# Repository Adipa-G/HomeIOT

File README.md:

# HomeIOT 🏠

A comprehensive IoT platform for managing embedded devices (ESP32/Pico). This platform supports creating modules in the serverside, assigning to devices so that these can be executed on the edge devices so that result is visible on the server.

## Key Features

- **Device Management**: Add devices from the web UI with one downloaded `main.py`, then monitor and control them across platforms (ESP32, Raspberry Pi Pico)
- **Module System**: Deploy and manage versioned Python modules on devices with remote execution and result tracking
- **Interactive Dev Commands**: Execute arbitrary Python code on devices for debugging and testing
- **Dashboard Analytics**: Real-time metrics on device health, module activity, and system status. The dashboard supports visual elements such as graphs and guages.
- **OTA Updates**: Over-the-air firmware updates with rollback support
- **Comprehensive Logging**: Device logs, module results, and execution tracking for troubleshooting

## Quick Start

### 

### Running the Server (30 seconds)

**Option 1: Direct .NET Execution** (for development)
```bash
# Clone and navigate to project
git clone <repo-url>
cd HomeIOT

# Run the API server
dotnet run --project api/src/api.csproj
```

Server starts at: `http://localhost:5228`

**Option 2: Docker Compose** (for easy setup)
```bash
docker-compose up -d
```

Server accessible at: `http://localhost:5228` (or your configured hostname)

### Initial Login

1. Open `http://localhost:5228` in your browser
2. Login with credentials:
   - **Username**: `Admin`
   - **Password**: `123`
3. ⚠️ **IMPORTANT**: Change the admin password immediately in the Web UI (Users section)
4. Verify setup: Dashboard should display "0 devices online"

---

## Project Structure

```
HomeIOT/
├── api/                    # .NET 10 Backend API
│   ├── src/               # API source code (controllers, services, data)
│   └── tests/             # xUnit tests
├── edge/                  # MicroPython edge runtime
│   ├── platforms/         # Platform-specific code (ESP32, Pico)
│   ├── shared/            # Common app logic and HAL
│   ├── bootstrap/         # First-boot installer embedded in the generated main.py
│   └── tools/             # Firmware release build and dev command scripts
├── web-ui/                # React + TypeScript Web Dashboard
├── data/                  # SQLite database (auto-created)
└── docs/                  # Detailed guides and references
```

## System Architecture

```mermaid
graph TB
    subgraph "Cloud/Server"
        API["API Server<br/>(C# .NET 10)"]
        DB["Database<br/>(SQLite)"]
        WEB["Web UI<br/>(React)"]
    end
    
    subgraph "Edge Devices"
        ESP32["ESP32<br/>(MicroPython)"]
        PICO["Pico<br/>(MicroPython)"]
    end
    
    subgraph "Admin Tools"
        TOOLS["Python Tools<br/>(build release)"]
    end
    
    WEB -->|Admin API| API
    API -->|Store/Query| DB
    ESP32 -->|Device API + OTA| API
    PICO -->|Device API + OTA| API
    TOOLS -->|Release| API
    
    style API fill:#0078d4
    style WEB fill:#61dafb
    style DB fill:#00a86b
    style ESP32 fill:#ff6b35
    style PICO fill:#004e89
```

### Layers Overview

| Layer | Technology | Role |
|-------|-----------|------|
| **Web UI** | React + TypeScript + Vite | Admin dashboard for managing devices, modules, users, and monitoring |
| **API** | C# .NET 10 + Entity Framework Core | REST API for device communication and admin operations |
| **Edge Runtime** | MicroPython | Firmware running on ESP32/Pico; polls for modules, executes commands |
| **Database** | SQLite | Stores devices, modules, logs, heartbeats, users, and execution results |

---

## Getting Started Guides

### For Setup & Deployment

| Guide | Purpose |
|-------|---------|
| [📖 Server Setup](docs/setup-server.md) | Install and configure the API server (direct .NET & Docker) |
| [📖 Edge Device Setup](docs/setup-edge-device.md) | Add ESP32/Pico devices and install firmware with the generated `main.py` |

### For Feature Usage

| Guide | Purpose |
|-------|---------|
| [📖 Dashboard](docs/features-dashboard.md) | Understand real-time metrics and system status |
| [📖 Device Management](docs/features-devices.md) | Add, re-provision, monitor, filter, and control devices |
| [📖 Module System](docs/features-modules.md) | Create, upload, assign, and execute modules |
| [📖 Data Visualizations](docs/features-visualizations.md) | Configure and use gauges, charts, and threshold colors |
| [📖 User Management](docs/features-users.md) | Manage admin users and authentication |
| [📖 Dev Commands](docs/features-dev-commands.md) | Execute remote code for debugging |

---

## Prerequisites

- **C# / .NET 10 SDK** — Required to run the API server
- **Python 3.11+ and [uv](https://docs.astral.sh/uv/)** — Required for edge tools (building firmware releases), the simulator and tests
- **Node.js 18+** — Required for Web UI development
- **Docker** (optional) — For containerized deployment via Docker Compose
- **mpremote** — To copy the generated `main.py` onto a device (`uvx mpremote`), or use Thonny

## Installation

### Dependencies Setup

```bash
# Clone the repository
git clone <repo-url>
cd HomeIOT

# Setup Python environment for edge tools (creates edge/.venv from edge/pyproject.toml and edge/uv.lock)
uv sync --project edge

# Setup Node dependencies for Web UI (optional for dev)
cd web-ui
npm install
cd ..
```

### First Run

1. Start the API server (see Quick Start above)
2. Web UI opens automatically or navigate to `http://localhost:5228`
3. Login with `Admin` / `123`
4. **IMPORTANT**: Change admin password immediately

---

## Testing

All code changes require corresponding tests. Run the full test suite:

```bash
# API tests (.NET)
dotnet test api/tests/homeiot.api.tests.csproj

# Edge tests (Python)
uv run --project edge pytest edge

# Edge type check (Python, config in edge/pyproject.toml)
uv run --project edge pyright -p edge
# Web UI tests (optional)
cd web-ui && npm test
```

---

## Development Workflow

### Typical Development Day

1. **Start API server** (background)
   ```bash
   dotnet run --project api/src/api.csproj
   ```

2. **Start Web UI dev server** (in new terminal)
   ```bash
   cd web-ui && npm run dev
   ```

3. **Access Web UI** at `http://localhost:5173` (Vite dev server)

4. **Make changes** to code and tests

5. **Run tests** to verify changes
   ```bash
   # Terminal 1: dotnet test api/tests/homeiot.api.tests.csproj
   # Terminal 2: uv run --project edge pytest edge
   # Terminal 3: npm test (in web-ui)
   ```

### Seeded Simulator Data

To load the demo device, module, variables, and visualizations, set `DevelopmentSeed:Enabled` to `true` in `api/src/appsettings.Development.json` before starting the API. The seed runs at API startup in the Development environment and only creates missing records.

The root `simulator-config.json` is configured for the seeded device (`simulator-device-1`). After starting the API, run the simulator from the repository root:

```bash
uv run --project edge python -m edge.simulator.worker --config simulator-config.json
```

The `demo-sensor` readings cycle through the configured threshold bands, including the default color below the first threshold. Let the simulator run for a few cycles to see the visualization colors and build chart history. The seed does not generate the simulator config; see [Server Setup](docs/setup-server.md) for the seed credentials and setup details.

### Code Conventions

- **C# / API**: One class per file, `PascalCase` file names, records for DTOs, `snake_case` JSON properties
- **Python / Edge**: MicroPython-compatible, pytest tests in `edge/shared/tests/`, type-checked with `pyright` (strict mode)
- **TypeScript / Web**: React components in `src/components/`, pages in `src/pages/`

See [.github/copilot-instructions.md](.github/copilot-instructions.md) for detailed conventions.

---

## Typical Workflows

### Setting Up a New Device

1. **Publish a firmware release** for the platform (once per version)
   ```bash
   uv run --project edge python edge/tools/build_artifact.py --platform esp32 --version 1.0.0
   ```
   When the API runs elsewhere (e.g. Docker), upload the release zip on the **OTA** page instead.

2. **Add the device** under **Devices > Add device**. Enter the device ID, platform, API URL (an IP or a hostname the device can resolve) and WiFi credentials. The browser downloads `main.py`.

3. **Install on the board.** Flash MicroPython, then copy the file and reset:
   ```bash
   mpremote cp main.py :main.py
   mpremote reset
   ```
   The installer writes `config.json`, connects to WiFi, and installs the latest release through OTA. Delete the downloaded `main.py` afterwards, because it contains the device key and WiFi password.

4. **Verify in Dashboard** — Device should appear online within 60 seconds

👉 Full guide: [Edge Device Setup](docs/setup-edge-device.md)

### Creating and Assigning a Module

1. Navigate to **Admin → Modules → Create Module**
2. Upload Python file with `exec()`-compatible code
3. Navigate to module detail → **Assign**
4. Select target devices and version
5. Device fetches and executes within 60 seconds
6. View results in device detail → **Module Results**

👉 Full guide: [Module System](docs/features-modules.md)

### Debugging a Device with Dev Commands

1. Navigate to **Admin → Dev Commands**
2. Write Python code (e.g., `print(device_info)`)
3. Select target device
4. Queue command
5. View result in real-time (device executes within 2 seconds)

👉 Full guide: [Dev Commands](docs/features-dev-commands.md)

---

## Configuration & Customization

### Server Configuration

Edit `api/src/appsettings.json`:

```json
{
  "RuntimeControl": {
    "NextHeartbeatMs": 60000,                    // Device heartbeat interval
    "DevPollIntervalMs": 2000,                   // Dev command polling
    "ModuleAssignmentPollIntervalMs": 60000      // Module assignment polling
  },
  "Admin": {
    "MasterUsername": "Admin",
    "MasterPassword": "YOUR_SECURE_PASSWORD"    // Change in production!
  }
}
```

For production, also change:
- `Jwt.SecretKey` — Use a cryptographically secure random key
- `ConnectionStrings.DefaultConnection` — Use production database
- Remove CORS localhost origins in `appsettings.json`

### Device Configuration

Device `config.json` is written on the device by the `main.py` installer from **Add device** / **Re-provision**, and includes:
- WiFi credentials and API key (encrypted, device-ID-bound)
- API URL and authentication
- Polling intervals and power settings
- Logging configuration

---

## Troubleshooting

### Device not appearing in dashboard
- Check API URL is correct and reachable from device (bare machine names like `homesvr` often don't resolve on the device; use an IP)
- Watch the `[bootstrap]` output with `mpremote repl` during first install
- Verify WiFi connection on device (use dev commands to test)
- Check device logs via `GET /api/devices/{id}/logs` in dashboard

### Module not executing
- Verify module syntax is correct (test locally first with dev commands)
- Check device is online (heartbeat recent)
- View module result for error details

### Web UI not loading
- Confirm API server is running on port 5228
- Check CORS configuration in `appsettings.json` includes your origin
- Clear browser cache and reload

For more, see the detailed guides linked above.

---

## License

GNU AFFERO GENERAL PUBLIC LICENSE Version 3

## Support

For issues, questions, or feature requests, please open an issue in the repository.

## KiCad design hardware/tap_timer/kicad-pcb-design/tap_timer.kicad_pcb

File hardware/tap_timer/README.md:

# Tap Timer

This project uses a Raspberry Pi Pico W to control a 12V water valve.
The board is designed to be able to be able to connect to multiple other sensors and also indicate different statuses using LEDs.

## How it works

`main.py` is a HomeIOT device module. Assign it with a short interval (for
example `interval_ms` = 60000). Each run checks whether the valve should be
open right now, so the valve closes within one interval of the window ending.
Keep the interval shorter than `VALVE_RUN_DURATION_MINUTES`, or a whole window
can be missed.

On each run the module:

- Reads the battery voltage from GPIO 26. This pin gets half of VSYS through a
  divider, so the voltage is doubled.
- Powers the rain sensor from GPIO 4 only while taking a reading, so the
  probe doesn't corrode.
- Reads the rain sensor's analog output on GPIO 27 as a wetness value from
  0 (dry) to 1023 (soaked). It also reads the digital output on GPIO 1, which
  is low while wet. The digital reading is only reported.
- Opens the valve on GPIO 0 from `VALVE_START_TIME` for
  `VALVE_RUN_DURATION_MINUTES`, as long as the current wetness is at or below
  `RAIN_THRESHOLD`. Once open, it stays open for the whole window even if it
  starts raining. There's no rain history: if the sensor dries out partway
  through a skipped window, the valve opens for the rest of it.
- Uses a fixed UTC+10 (AEST) clock with no daylight saving, so a 17:00 start
  happens at 18:00 by the clock in summer.
- Keeps the valve closed until the clock is synced, and closes it if the run
  fails.
- Opens the valve when `TURN_VALVE_ON_MANUALLY` is set to `true`, ignoring the
  schedule, rain and clock sync. It stays open until the variable is set back
  to `false`.

The module stores nothing between runs. It reads the valve and indicator pins
back to remember what it decided last time. A reboot sets them all low.

The source is kept small on purpose. The Pico W ran out of memory compiling an
11 KB version of this module.

### Indicator LEDs

| Pin    | On when |
|--------|---------|
| GPIO 2 | The current wetness is above `RAIN_THRESHOLD`. |
| GPIO 3 | Rain skipped today's window. It stays on until midnight. |

### Module variables

These can be overridden with module variables. If a variable isn't set, the
default is used.

| Variable                     | Default   | Description |
|------------------------------|-----------|-------------|
| `VALVE_START_TIME`           | `"17:00"` | Start time (`HH:MM`, AEST). |
| `VALVE_RUN_DURATION_MINUTES` | `10`      | How long the valve stays open. |
| `RAIN_THRESHOLD`             | `100`     | Wetness (0-1023) above which the window is skipped. |
| `TURN_VALVE_ON_MANUALLY`     | `false`   | Hold the valve open regardless of schedule and rain. Use a boolean variable with a toggle control. |

## PCB design and power

The PCB is designed in KiCad, with the project files located in
[`kicad-pcb-design`](kicad-pcb-design). It takes a solar panel input and charge a 18650 battery and use this to run the timer.

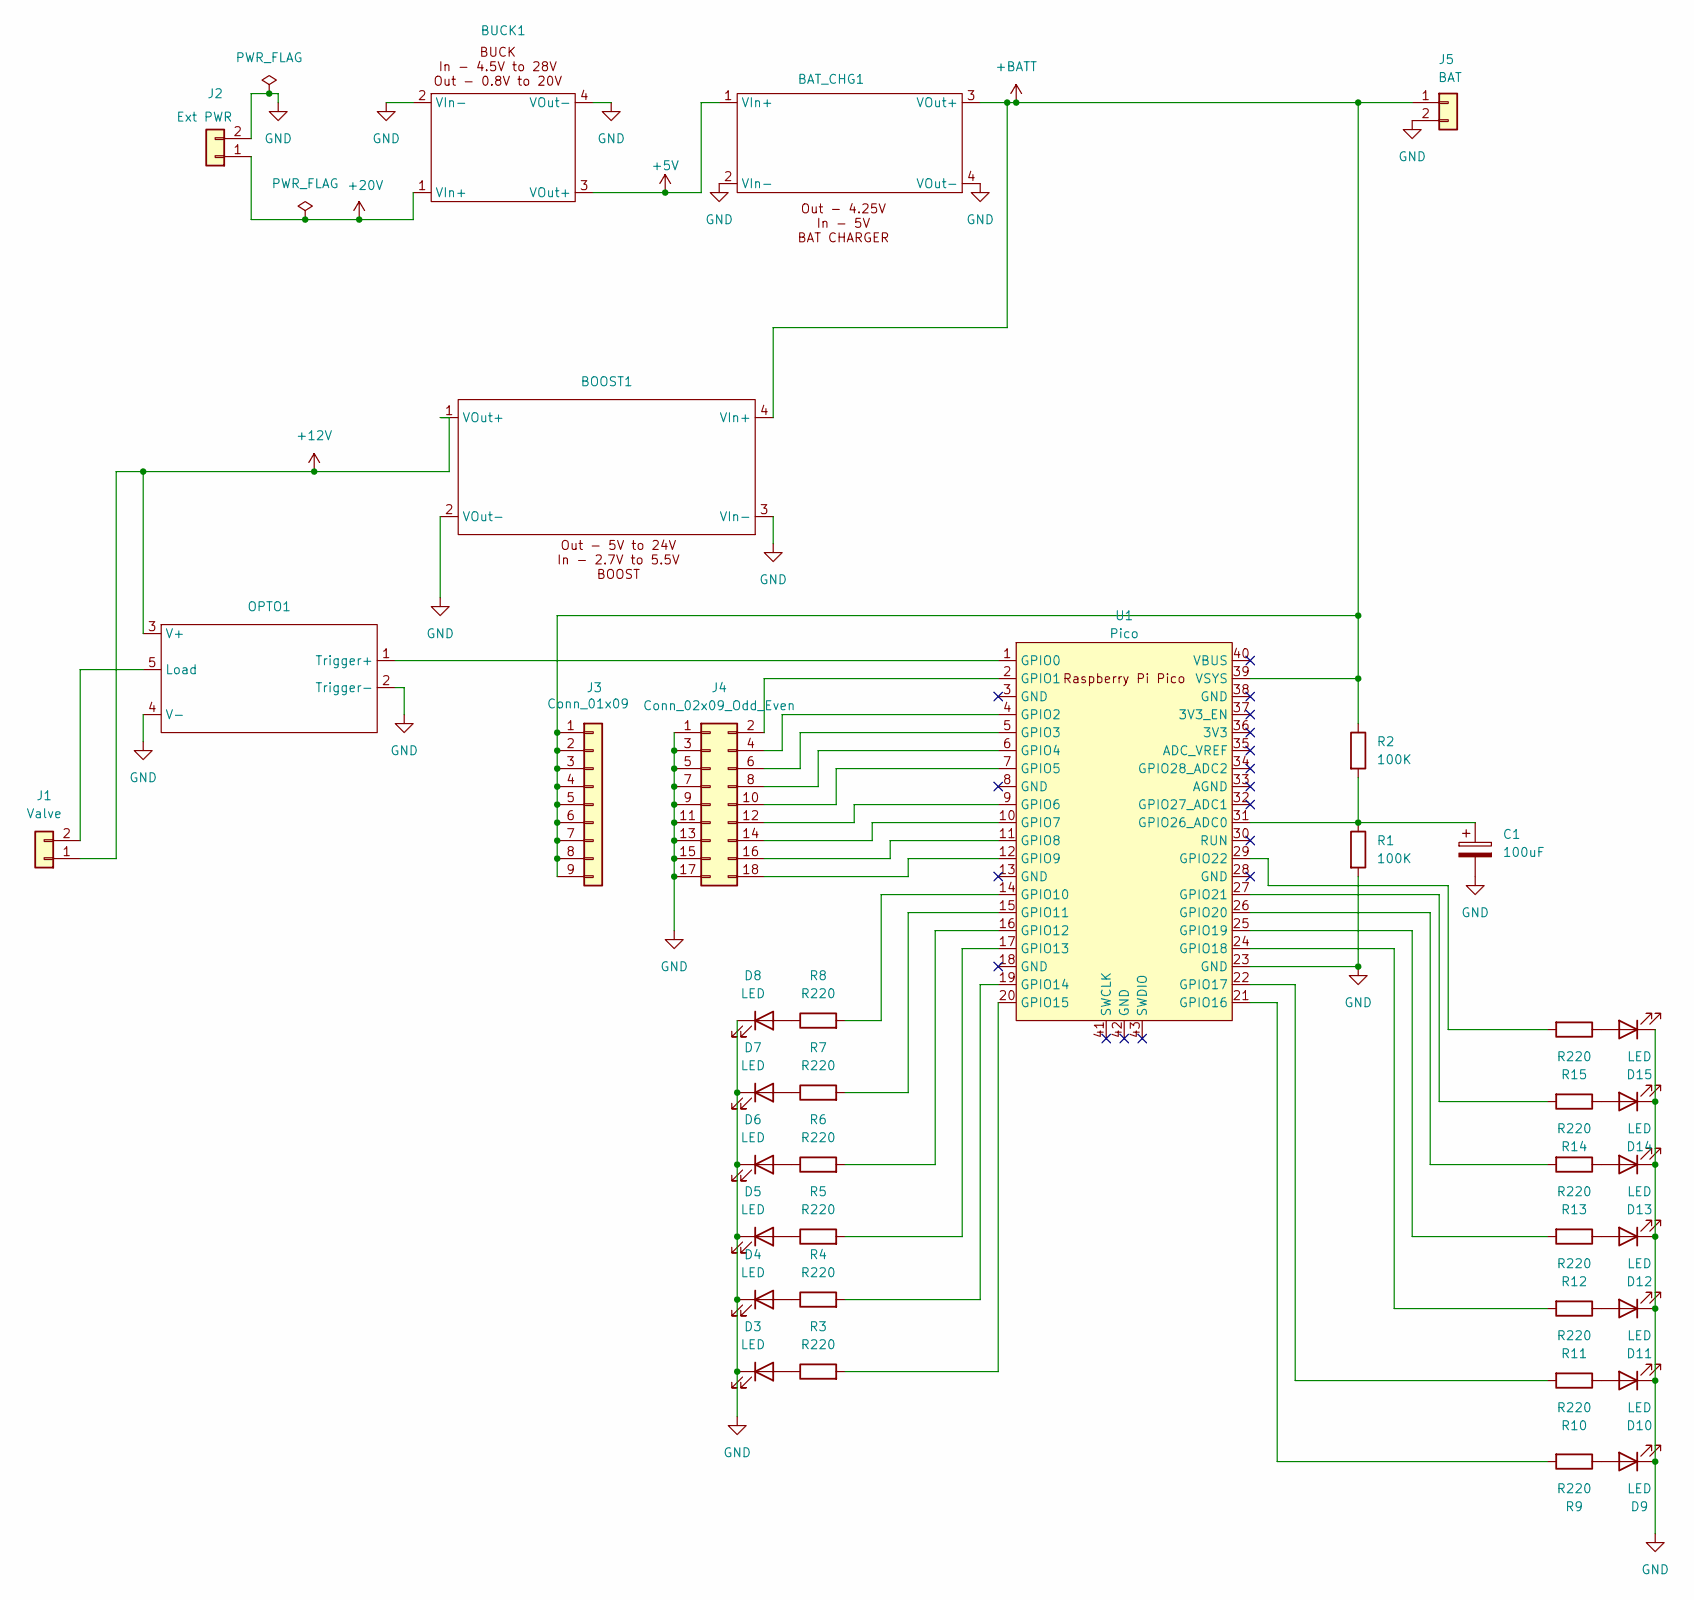
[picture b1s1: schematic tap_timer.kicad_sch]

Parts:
BAT_CHG1: BAT_CHG_1
BOOST1: BOOST_1
BUCK1: BUCK_1
C1: 100uF; CP_Radial_D10.0mm_P7.50mm
D3, D4, D5, D6, D7, D8, D9, D10, D11, D12, D13, D14, D15: LED; LED_D3.0mm
J1: Valve; JST_PH_B2B-PH-K_1x02_P2.00mm_Vertical
J2: Ext PWR; JST_PH_B2B-PH-K_1x02_P2.00mm_Vertical
J3: Conn_01x09; PinHeader_1x09_P2.54mm_Vertical
J4: Conn_02x09_Odd_Even; PinHeader_2x09_P2.54mm_Vertical
J5: BAT; JST_PH_B2B-PH-K_1x02_P2.00mm_Vertical
OPTO1: OPTO_1
R1, R2: 100K; R_Axial_DIN0207_L6.3mm_D2.5mm_P10.16mm_Horizontal
R3, R4, R5, R6, R7, R8, R9, R10, R11, R12, R13, R14, R15: R220; R_Axial_DIN0207_L6.3mm_D2.5mm_P10.16mm_Horizontal
U1: Pico; RPi_Pico_SMD_TH

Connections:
+5V: BAT_CHG1.1 (VIn+), BUCK1.3 (VOut+)
+12V: BOOST1.1 (VOut+), J1.1, OPTO1.3 (V+)
+20V: BUCK1.1 (VIn+), J2.1
+BATT: BAT_CHG1.3 (VOut+), BOOST1.4 (VIn+), J3.1, J3.2, J3.3, J3.4, J3.5, J3.6, J3.7, J3.8, J3.9, J5.1, R2.1, U1.39 (VSYS)
GND: BAT_CHG1.2 (VIn-), BAT_CHG1.4 (VOut-), BOOST1.2 (VOut-), BOOST1.3 (VIn-), BUCK1.2 (VIn-), BUCK1.4 (VOut-), C1.2, D3.1 (K), D4.1 (K), D5.1 (K), D6.1 (K), D7.1 (K), D8.1 (K), D9.1 (K), D10.1 (K), D11.1 (K), D12.1 (K), D13.1 (K), D14.1 (K), D15.1 (K), J2.2, J4.1, J4.3, J4.5, J4.7, J4.9, J4.11, J4.13, J4.15, J4.17, J5.2, OPTO1.2 (Trigger-), OPTO1.4 (V-), R1.2, U1.23 (GND)
unnamed: D3.2 (A), R3.1
unnamed: D4.2 (A), R4.1
unnamed: D5.2 (A), R5.1
unnamed: D6.2 (A), R6.1
unnamed: D7.2 (A), R7.1
unnamed: D8.2 (A), R8.1
unnamed: D9.2 (A), R9.1
unnamed: D10.2 (A), R10.1
unnamed: D11.2 (A), R11.1
unnamed: D12.2 (A), R12.1
unnamed: D13.2 (A), R13.1
unnamed: D14.2 (A), R14.1
unnamed: D15.2 (A), R15.1
unnamed: J1.2, OPTO1.5 (Load)
unnamed: J4.2, U1.2 (GPIO1)
unnamed: J4.4, U1.4 (GPIO2)
unnamed: J4.6, U1.5 (GPIO3)
unnamed: J4.8, U1.6 (GPIO4)
unnamed: J4.10, U1.7 (GPIO5)
unnamed: J4.12, U1.9 (GPIO6)
unnamed: J4.14, U1.10 (GPIO7)
unnamed: J4.16, U1.11 (GPIO8)
unnamed: J4.18, U1.12 (GPIO9)
unnamed: OPTO1.1 (Trigger+), U1.1 (GPIO0)
unnamed: R8.2, U1.14 (GPIO10)
unnamed: R7.2, U1.15 (GPIO11)
unnamed: R6.2, U1.16 (GPIO12)
unnamed: R5.2, U1.17 (GPIO13)
unnamed: R4.2, U1.19 (GPIO14)
unnamed: R3.2, U1.20 (GPIO15)
unnamed: R9.2, U1.21 (GPIO16)
unnamed: R10.2, U1.22 (GPIO17)
unnamed: R11.2, U1.24 (GPIO18)
unnamed: R12.2, U1.25 (GPIO19)
unnamed: R13.2, U1.26 (GPIO20)
unnamed: R14.2, U1.27 (GPIO21)
unnamed: R15.2, U1.29 (GPIO22)
unnamed: C1.1, R1.1, R2.2, U1.31 (GPIO26_ADC0)

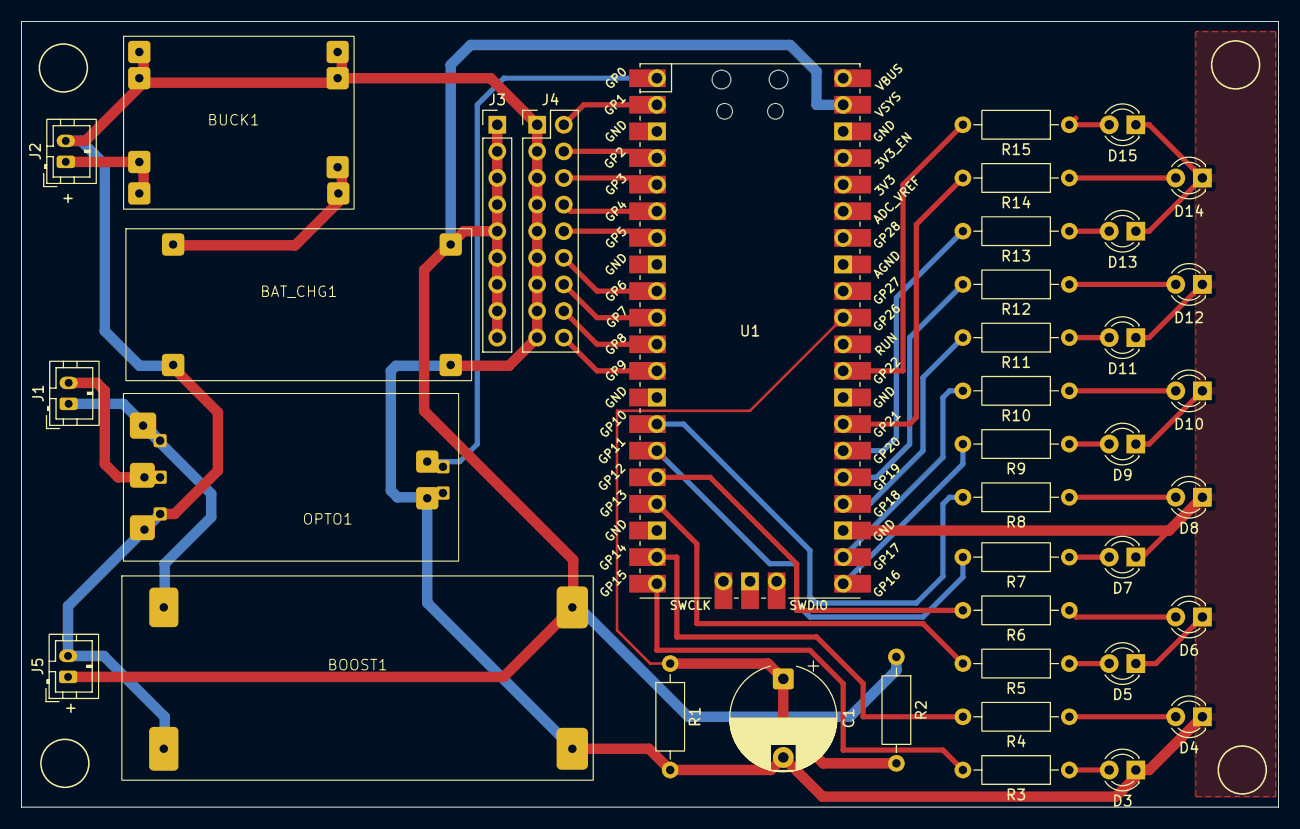
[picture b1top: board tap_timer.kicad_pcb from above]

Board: 2 copper layers, 120.0 x 75.0 mm, 39 parts (0 on the bottom side), 43 nets.

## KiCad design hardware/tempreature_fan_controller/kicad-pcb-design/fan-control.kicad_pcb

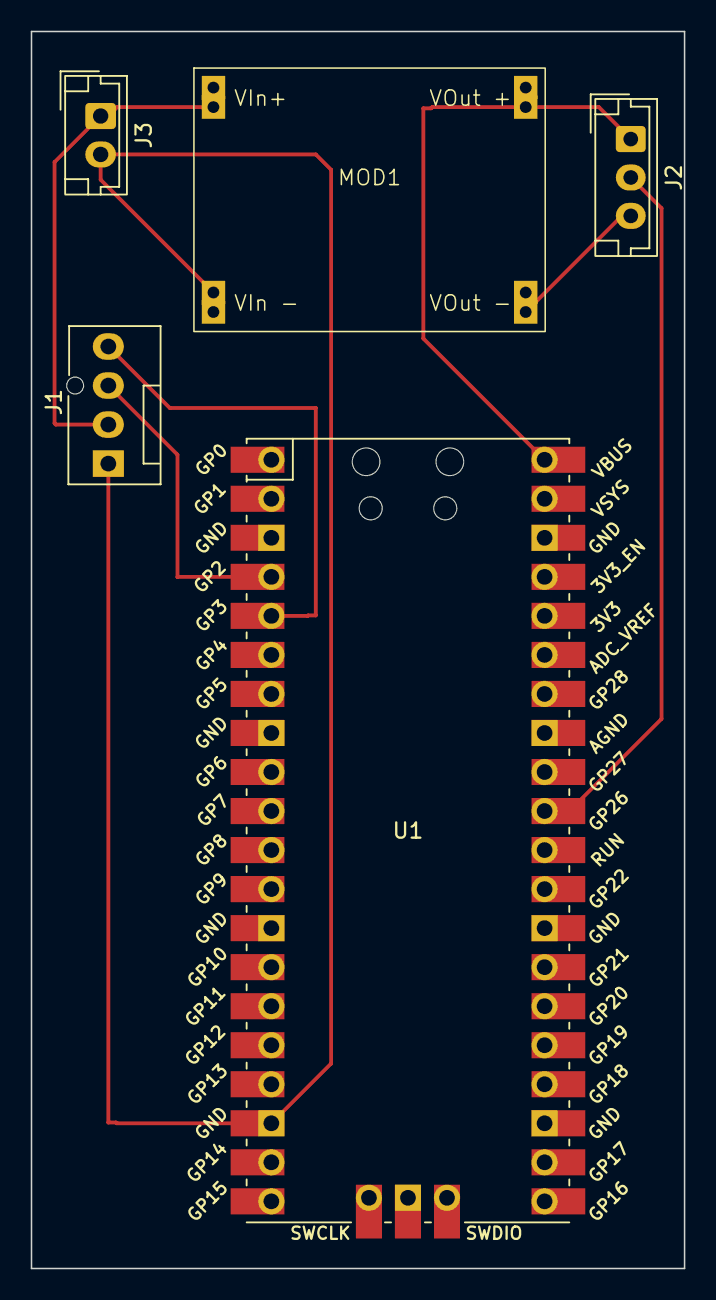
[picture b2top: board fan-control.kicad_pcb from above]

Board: 2 copper layers, 42.5 x 80.5 mm, 5 parts (0 on the bottom side), 6 nets.

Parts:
J1: Fan; FanPinHeader_1x04_P2.54mm_Vertical
J2: Temp Sensor; JST_EH_B3B-EH-A_1x03_P2.50mm_Vertical
J3: PWR; JST_EH_B2B-EH-A_1x02_P2.50mm_Vertical
MOD1: BUCK_CONVERTER; BUCK_COVERTER
U1: Pico; RPi_Pico_SMD_TH

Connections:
+5V: J2.1, MOD1.3 (VOut+), U1.40 (VBUS)
+12V: J1.2, J3.1, MOD1.1 (VIn+)
GND: J1.1, J2.3, J3.2, MOD1.2 (VIn-), MOD1.4 (VOut-), U1.3 (GND), U1.18 (GND)
unnamed: J1.3, U1.4 (GPIO2)
unnamed: J1.4, U1.5 (GPIO3)
unnamed: J2.2, U1.31 (GPIO26_ADC0)

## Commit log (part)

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2026-03-03 Initial stuff
2026-03-05 refactor
2026-03-07 provision
2026-03-11 dev commands and modules
2026-03-13 power saving
2026-03-15 the boot and main loop works fine on a real ESP32
2026-03-21 Ping endpoint
2026-03-23 get comms up
2026-03-27 dev command
2026-03-29 stability improvements
2026-04-02 other controllers
2026-04-04 OTA controller
2026-04-06 Dev commands
2026-04-08 React UI
2026-04-10 React UI tests
2026-04-12 more fixes
2026-04-14 module fixes
2026-04-16 Fixed the OTA performance
2026-04-18 Device Modules
2026-04-20 More reliable update
2026-04-22 NTP time sync
2026-04-26 coding standards
2026-04-28 module assignment
2026-04-30 layout fixes
2026-05-02 making logs to work during OTA
2026-05-04 module variables
2026-05-12 login redirect
2026-05-14 adding a bit more refereces to be able to run a web request
2026-05-18 variable assignment panel
2026-05-20 variable override per device
2026-05-22 Last bits for Pico support
2026-05-24 Documentation
2026-05-26 adding the build and test
2026-06-01 container start
2026-06-01 playwright
2026-06-01 push to docker
2026-06-02 push to docker multi platform
2026-06-02 Fix the URL
2026-06-02 Fix the folders
2026-06-19 update LICENSE
2026-06-19 adding mock edge device
2026-06-19 Fix the tests
2026-06-20 adding the edit UI
2026-06-20 adding the visual UI
2026-06-20 dotnet unit tests
2026-06-20 UI tests
2026-06-20 UI fixes
2026-06-20 OTA fixes
2026-06-21 Fix delete version bug
2026-06-21 guage
2026-06-21 fix other types of visuals
2026-06-21 documentation update
